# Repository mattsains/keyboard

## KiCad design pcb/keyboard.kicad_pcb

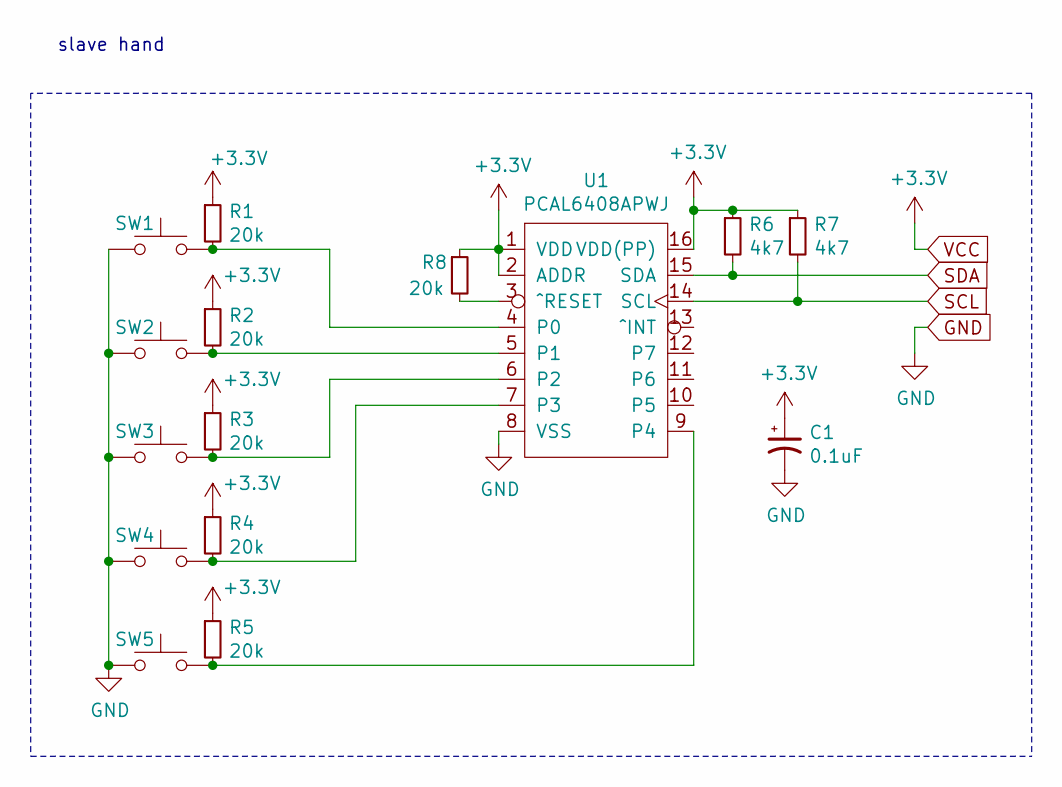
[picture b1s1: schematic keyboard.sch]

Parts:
C1: 0.1uF; C_1206_3216Metric
R1, R2, R3, R4, R5, R8: 20k; R_1206_3216Metric
R6, R7: 4k7; R_1206_3216Metric
SW1, SW2, SW3, SW4, SW5: SW_Push; PinSocket_1x02_P2.54mm_Vertical
U1: PCAL6408APWJ; TSSOP-16_4.4x5mm_P0.65mm

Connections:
GND: C1.2, SW1.1, SW2.1, SW3.1, SW4.1, SW5.1, U1.8 (VSS); also elsewhere on the board
unnamed: R1.2, SW1.2, U1.4 (P0)
unnamed: R2.2, SW2.2, U1.5 (P1)
unnamed: R3.2, SW3.2, U1.6 (P2)
unnamed: R4.2, SW4.2, U1.7 (P3)
unnamed: R5.2, SW5.2, U1.9 (P4)
unnamed: R8.2, U1.3 (^RESET)
SCL: R7.2, U1.14 (SCL); also elsewhere on the board
SDA: R6.2, U1.15 (SDA); also elsewhere on the board
VCC: C1.1, R1.1, R2.1, R3.1, R4.1, R5.1, R6.1, R7.1, R8.1, U1.1 (VDD), U1.2 (ADDR), U1.16 (VDD(PP)); also elsewhere on the board

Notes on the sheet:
slave hand

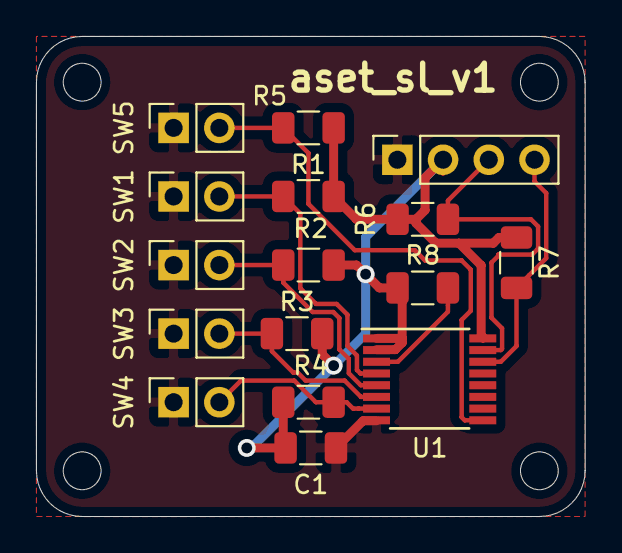
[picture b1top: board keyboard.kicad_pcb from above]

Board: 2 copper layers, 30.5 x 26.7 mm, 16 parts (0 on the bottom side), 10 nets.

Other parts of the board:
MAIN: PinSocket_1x04_P2.54mm_Vertical

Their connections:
GND: MAIN.1; also elsewhere on the board
SCL: MAIN.4; also elsewhere on the board
SDA: MAIN.3; also elsewhere on the board
VCC: MAIN.2; also elsewhere on the board

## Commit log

2019-11-11 aset_s1_v1
2020-01-22 Add code
2020-02-16 move arduino project to be compatible with IDE
2020-02-16 Upload enclosure design
2020-02-17 Move to platform IO for arduino code
2020-02-17 remove autogenerated code from version control
2020-02-17 set up python package for tutor
2020-02-17 Secretly announce held keys over HID
2020-02-17 Working tutor UI
2020-02-20 Tutor is working!
2020-02-22 switch shift and space keys
    Fixes #1
2020-02-22 Add uppercase punctuation support in firmware
2020-02-22 simplify code
2020-02-22 fix trivial uppercase case bug
2020-02-22 support uppercase punctuation in tutor
